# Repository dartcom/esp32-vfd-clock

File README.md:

# esp32-vfd-clock
A clock using the IV-6 vdf tubes

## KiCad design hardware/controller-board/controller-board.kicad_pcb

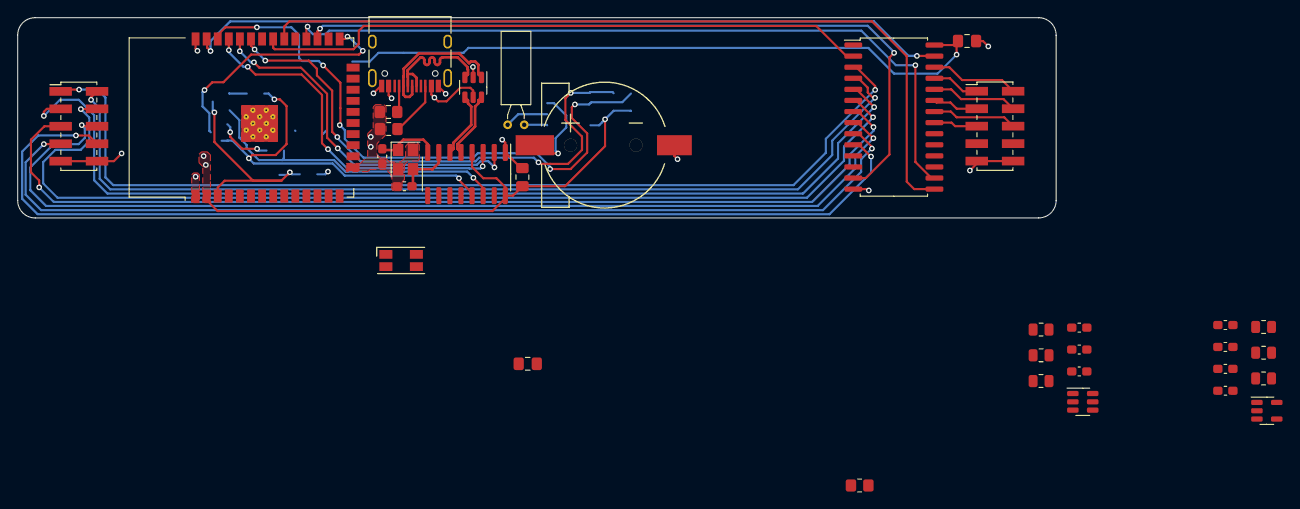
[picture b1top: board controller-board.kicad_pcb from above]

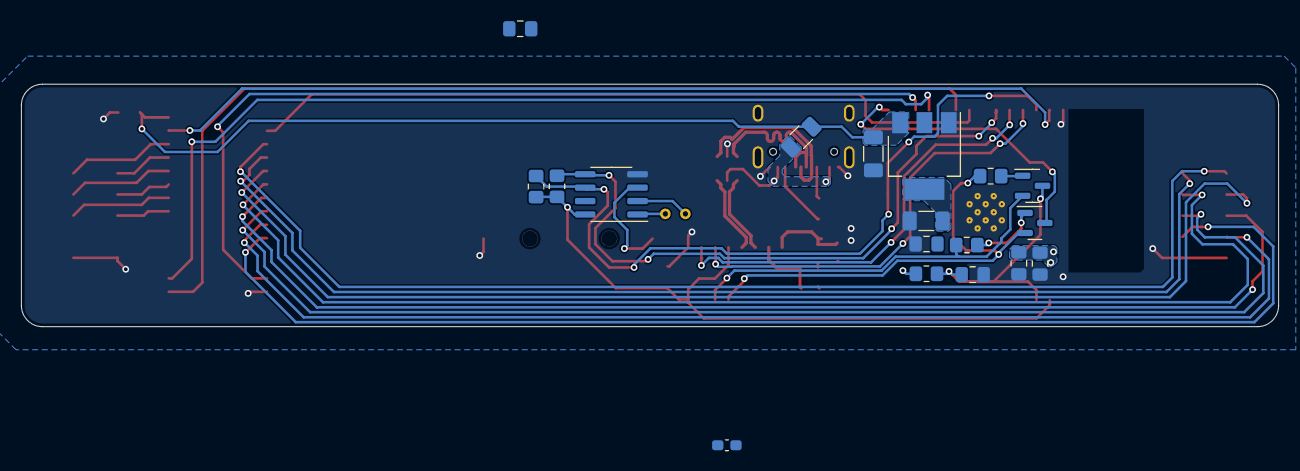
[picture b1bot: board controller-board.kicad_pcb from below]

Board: 2 copper layers, 119.0 x 22.9 mm, 52 parts (18 on the bottom side), 56 nets.

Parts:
BT1: Battery_Cell; BAT-SMD_CR1220-2
C1, C7, C11, C13: 0.1uf; C_0805_2012Metric_Pad1.18x1.45mm_HandSolder
C2, C3: 32pf; C_0603_1608Metric_Pad1.08x0.95mm_HandSolder
C4, C8, C9: 10uf; C_0805_2012Metric_Pad1.18x1.45mm_HandSolder
C5: 0.1uf; C_0603_1608Metric_Pad1.08x0.95mm_HandSolder
C6: 1uf; C_0805_2012Metric_Pad1.18x1.45mm_HandSolder
C10, C12: 22uf; C_1206_3216Metric_Pad1.33x1.80mm_HandSolder
C14, C15, C16, C17, C18: 22uf; C_0603_1608Metric_Pad1.08x0.95mm_HandSolder
C19, C20: 1nf; C_0603_1608Metric_Pad1.08x0.95mm_HandSolder
D1: LED_RGBA; LED_RGB_1210
F1: 1A; Fuse_1206_3216Metric
J1, J2: Conn_02x05_Top_Bottom; PinHeader_2x05_P2.00mm_Vertical_SMD
J3: USB_C_Receptacle_USB2.0; USB_C_Receptacle_HRO_TYPE-C-31-M-12
Q1, Q2: SI2308DS; SOT-23
R1, R2: 5k1; R_0805_2012Metric_Pad1.20x1.40mm_HandSolder
R3, R4, R8: 220; R_0805_2012Metric_Pad1.20x1.40mm_HandSolder
R5: 10k; R_0805_2012Metric_Pad1.20x1.40mm_HandSolder
R6, R7: 4k7; R_0805_2012Metric_Pad1.20x1.40mm_HandSolder
R11, R12, R13, R14, R15, R16: R; R_0805_2012Metric
U1: USBLC6-2SC6; SOT-23-6
U2: CH340G; SOIC-16_3.9x9.9mm_P1.27mm
U3: ESP32-WROOM-32
U4: AP1117-33; SOT-223-3_TabPin2
U5: MAX6921; SOIC-28W_7.5x17.9mm_P1.27mm
U6: DS1307Z+; SOIC-8_3.9x4.9mm_P1.27mm
U7: MT3608; SOT-23-6
U8: TLV62568DBV; SOT-23-5
Y1: 12mhz; Crystal_SMD_3225-4Pin_3.2x2.5mm
Y2: Crystal; Crystal_C38-LF_D3.0mm_L8.0mm_Horizontal

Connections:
+3V0: BT1.1 (+), U6.3 (VBAT)
+3V3: C1.1, C4.1, C5.1, C7.1, C8.1, C9.1, C12.1, R5.2, R6.2, R7.2, R8.2, U2.4 (V3), U2.16 (VCC), U3.2 (VDD), U4.2 (VO), U6.8 (VCC)
+5V: C10.1, C11.1, C13.1, C14.1, C18.1, F1.2, U4.3 (VI), U5.28 (VCC), U7.5 (IN), U8.4 (VIN)
/A: J1.1, U5.3 (OUT19)
/B: J1.2, U5.4 (OUT18)
/BLANK: U3.27 (IO16), U5.13 (BLANK)
/C: J1.3, U5.5 (OUT17)
/D: J1.4, U5.6 (OUT16)
/DAC_1: R13.2, U3.10 (IO25)
/DAC_2: R16.1, U3.11 (IO26)
/DTR: Q2.2 (S), R3.1, U2.13 (~DTR)
/Dot: J1.8, U5.10 (OUT12)
/E: J1.5, U5.7 (OUT15)
/EN: C6.2, Q1.3 (D), R5.1, U3.3 (EN)
/EN_1: U3.12 (IO27), U7.4 (EN)
/EN_2: U3.8 (IO32), U8.1 (EN)
/F: J1.6, U5.8 (OUT14)
/G: J1.7, U5.9 (OUT13)
/GPIO_0: Q2.3 (D), U3.25 (IO0)
/GPIO_1_TX: U2.3 (RXD), U3.35 (TXD0/IO1)
/GPIO_3_RX: U2.2 (TXD), U3.34 (RXD0/IO3)
/I2C_SCL: R6.1, U3.36 (IO22), U6.6 (SCL)
/I2C_SDA: R7.1, U3.33 (IO21), U6.5 (SDA)
/LED_B: D1.3 (BK), U3.13 (IO14)
/LED_G: D1.2 (GK), U3.16 (IO13)
/LED_R: D1.1 (RK), U3.14 (IO12)
/LOAD: U3.28 (IO17), U5.16 (LOAD)
/RTS: Q1.2 (S), R4.1, U2.14 (~RTS)
/Seg_1: J2.1, U5.25 (OUT1)
/Seg_2: J2.2, U5.26 (OUT0)
/Seg_3: J2.3, U5.23 (OUT3)
/Seg_4: J2.4, U5.24 (OUT2)
/Seg_5: J2.5, U5.21 (OUT5)
/Seg_6: J2.6, U5.22 (OUT4)
/USB_+: J3.A6 (D+), J3.B6 (D+), U1.1 (I/O1)
/USB_-: J3.A7 (D-), J3.B7 (D-), U1.3 (I/O2)
/VSPI_CLK: U3.30 (IO18), U5.15 (CLK)
/VSPI_MISO: U3.31 (IO19), U5.2 (DOUT)
/VSPI_MOSI: U3.37 (IO23), U5.27 (DIN)
/V_FILLAMENT: C16.1, C17.1, C20.1, J2.7, J2.8, R14.1
/V_SEGMENT: C15.1, C19.1, R11.1, U5.1 (VBB)
/usb_+: U1.6 (I/O1), U2.5 (UD+)
/usb_-: U1.4 (I/O2), U2.6 (UD-)
GND: BT1.2 (-), C1.2, C2.1, C3.2, C4.2, C5.2, C6.1, C7.2, C8.2, C9.2, C10.2, C11.2, C12.2, C13.2, C14.2, C15.2, C16.2, C17.2, C18.2, J1.9, J1.10, J2.9, J2.10, J3.A1 (GND), J3.A12 (GND), J3.B1 (GND), J3.B12 (GND), J3.S1 (SHIELD), R1.1, R2.1, R12.2, R15.2, U1.2 (GND), U2.1 (GND), U3.1 (GND), U3.15 (GND), U3.38 (GND), U3.39 (GND), U4.1 (GND), U5.14 (GND), U6.4 (GND), U7.2 (GND), U8.2 (GND), Y1.2, Y1.4
unnamed: D1.4 (A), R8.1
unnamed: J3.A8 (SBU1), R2.2
unnamed: J3.B8 (SBU2), R1.2
unnamed: Q1.1 (G), R3.2
unnamed: Q2.1 (G), R4.2
unnamed: C2.2, U2.7 (XI), Y1.3
unnamed: C3.1, U2.8 (XO), Y1.1
unnamed: U6.1 (X1), Y2.1
unnamed: U6.2 (X2), Y2.2
unnamed: C19.2, R11.2, R12.1, R13.1, U7.3 (FB)
unnamed: C20.2, R14.2, R15.1, R16.2, U8.5 (FB)
VBUS: F1.1, J3.A4 (VBUS), J3.A9 (VBUS), J3.B4 (VBUS), J3.B9 (VBUS), U1.5 (VBUS)

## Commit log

2023-09-27 started on the schamtic and pcb
